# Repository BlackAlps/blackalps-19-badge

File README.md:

# BlackAlps badge

This repository contains the blackAlps badge source, along with utilities to create user-created apps.

## Easy start

The easiest way is to use [Ampy](https://github.com/scientifichackers/ampy/tree/c0b568cf12b017bd9dfd7d61a7132b7d760278a0)
to store new files on the badge. To install on MacOS or GNU/Linux, simply type:

```bash
pip3 install --user adafruit-ampy
```

Once it's installed, on MacOS you can type the following to have a look at the
badge and to upload a new file:

```bash
ampy --port /dev/tty.usbserial-14410 ls
```

You can add the [template](utils/app_template/template.py) to the [apps](badgeOS/apps)
directory, and then upload it to the badge:

```bash
cp utils/app_template/template.py badgeOS/apps/myapp.py
ampy --port /dev/tty.usbserial-14410 put ./badgeOS/apps/myapp.py apps/myapp.py
```

Now you need to reset the board. The `ampy reset` doesn't seem to work, so you
need to remove and add the battery again.

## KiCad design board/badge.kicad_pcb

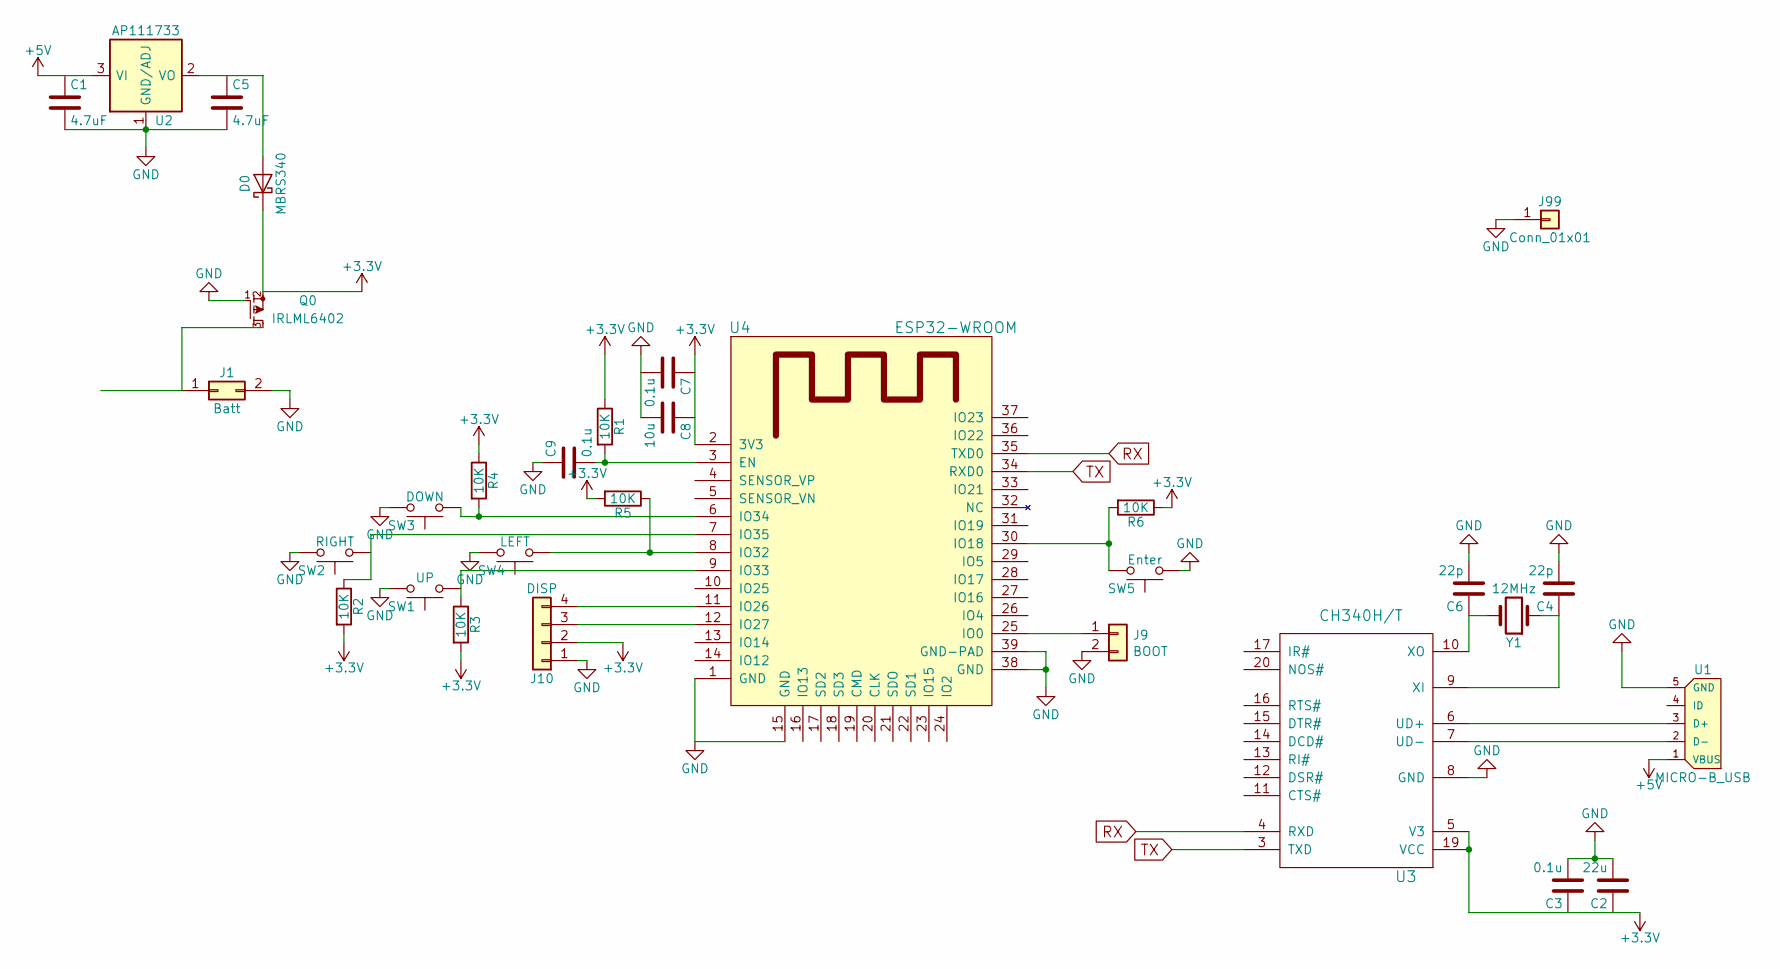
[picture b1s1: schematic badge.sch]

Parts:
C1, C5: 4.7uF; C_0805
C2: 22u; C_0805
C3, C7, C9: 0.1u; C_0805
C4, C6: 22p; C_0805
C8: 10u; C_0805
D0: MBRS340; D_SMC
J1: Batt; Pin_Header_Straight_1x02_Pitch2.54mm
J9: BOOT; Pin_Header_Straight_1x02_Pitch2.54mm
J10: DISP; Pin_Header_Straight_1x04_Pitch2.54mm
J99: Conn_01x01; 1pin
Q0: IRLML6402; SOT-23
R1, R2, R3, R4, R5, R6: 10K; R_0805
SW1: UP; SW_SPST_FSMSM
SW2: RIGHT; SW_SPST_FSMSM
SW3: DOWN; SW_SPST_FSMSM
SW4: LEFT; SW_SPST_FSMSM
SW5: Enter; SW_SPST_FSMSM
U1: MICRO-B_USB
U2: AP111733; SOT-223
U3: CH340H/T; SSOP-20_5.3x7.2mm_Pitch0.65mm
U4: ESP32-WROOM
Y1: 12MHz; NX5032GA-12.000000MHZ-LN-CD-1

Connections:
+3V3: D0.1 (K), J10.2, Q0.2 (S), R1.1, R2.2, R3.2, R4.1, R5.2, R6.1, U3.5 (V3), U3.19 (VCC), U4.2 (3V3)
+5V: U1.1 (VBUS), U2.3 (VI)
GND: C1.2, C2.2, C3.2, C4.2, C5.2, C6.2, C8.2, C9.1, J1.2, J9.2, J10.1, J99.1, Q0.1 (G), SW1.2, SW2.2, SW3.2, SW4.2, SW5.1, U1.5 (GND), U2.1 (GND/ADJ), U3.8 (GND), U4.1 (GND), U4.15 (GND), U4.38 (GND), U4.39 (GND-PAD)
unnamed: C4.1, U3.9 (XI), Y1.1
unnamed: C6.1, U3.10 (XO), Y1.2
unnamed: C9.2, R1.2, U4.3 (EN)
unnamed: D0.2 (A), U2.2 (VO), U2.4 (VO)
unnamed: J1.1, Q0.3 (D)
unnamed: J9.1, U4.25 (IO0)
unnamed: J10.3, U4.12 (IO27)
unnamed: J10.4, U4.11 (IO26)
unnamed: R2.1, U4.7 (IO35)
unnamed: R3.1, U4.9 (IO33)
unnamed: R4.2, SW3.1, U4.6 (IO34)
unnamed: R5.1, SW4.1, U4.8 (IO32)
unnamed: R6.2, SW5.2, U4.30 (IO18)
unnamed: U1.2 (D-), U3.7 (UD-)
unnamed: U1.3 (D+), U3.6 (UD+)
RX: U3.4 (RXD), U4.35 (TXD0)
TX: U3.3 (TXD), U4.34 (RXD0)

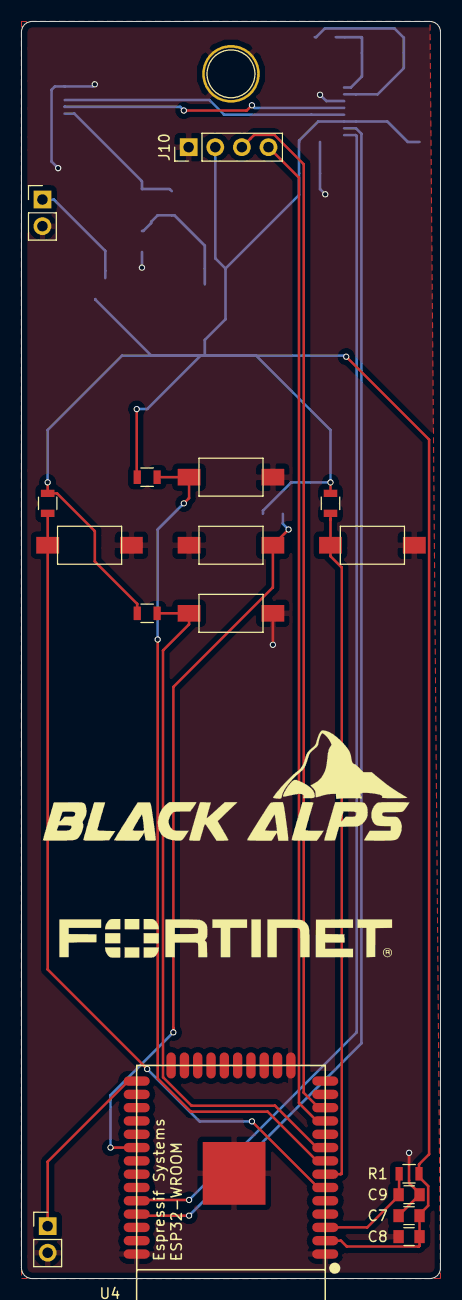
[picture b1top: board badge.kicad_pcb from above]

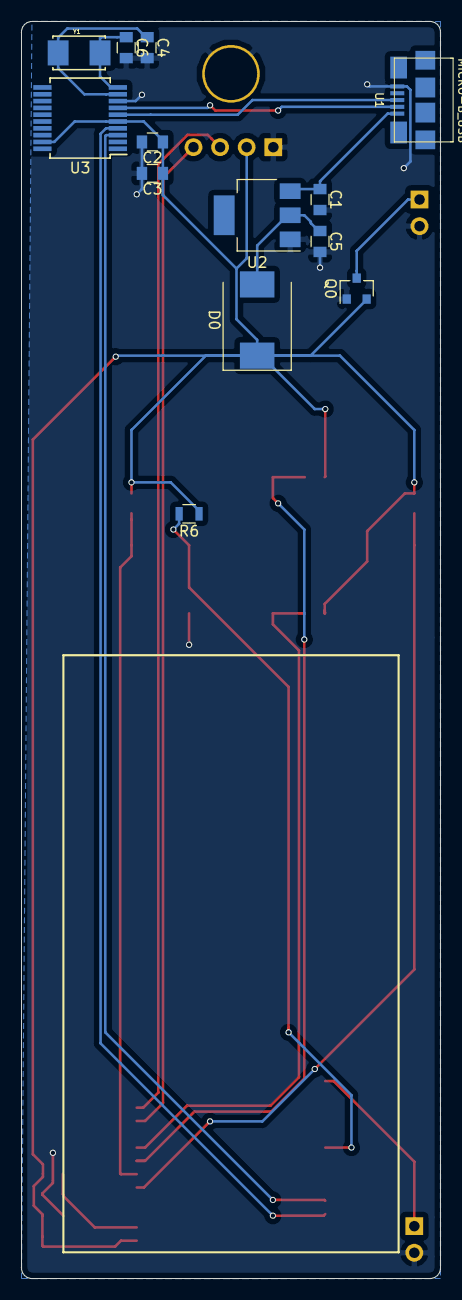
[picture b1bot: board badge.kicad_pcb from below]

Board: 2 copper layers, 40.0 x 120.0 mm, 31 parts (13 on the bottom side), 20 nets.

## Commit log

2019-11-05 Add firmware
2019-11-05 Add badgeOS files
2019-11-05 Add ampy as submodule
2019-11-05 Add bmp2oled
2019-11-05 Add app template
2019-11-05 Add README
2019-11-07 Adding instructions for first-timers
2019-11-07 Adding simulator
2019-11-07 Add slides
2019-11-07 Add simple beer counter app.
2019-11-07 Add Wifi Scanner app
2019-11-07 The game of life
2019-11-07 add two apps: one with pico le croco, the other to vote for my talk
2019-11-07 application that displays ph0wn logo
2019-11-07 Add clock app
2019-11-07 Add GreHack Lame Demo :-)
2019-11-07 screen: Fix fill rect args
    Args 2 and 3 are width but not coordinates.
2019-11-07 Add fancy keyboard
2019-11-08 Add party parrot app. See https://cultofthepartyparrot.com/ for inspiration
2019-11-08 Remove unused import
2019-11-09 Add board schematics
2021-11-25 Add udev rules for the badge
2021-11-27 Ph0wn 2021 app
2021-11-30 Update ph0wn application
2021-12-04 Update server address
